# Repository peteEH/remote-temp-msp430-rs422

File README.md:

# remote-temp-msp430-rs422
Remote Temperature Sensor Node - TMP10 - RS-422 or RS-485 based - MSP430G2553

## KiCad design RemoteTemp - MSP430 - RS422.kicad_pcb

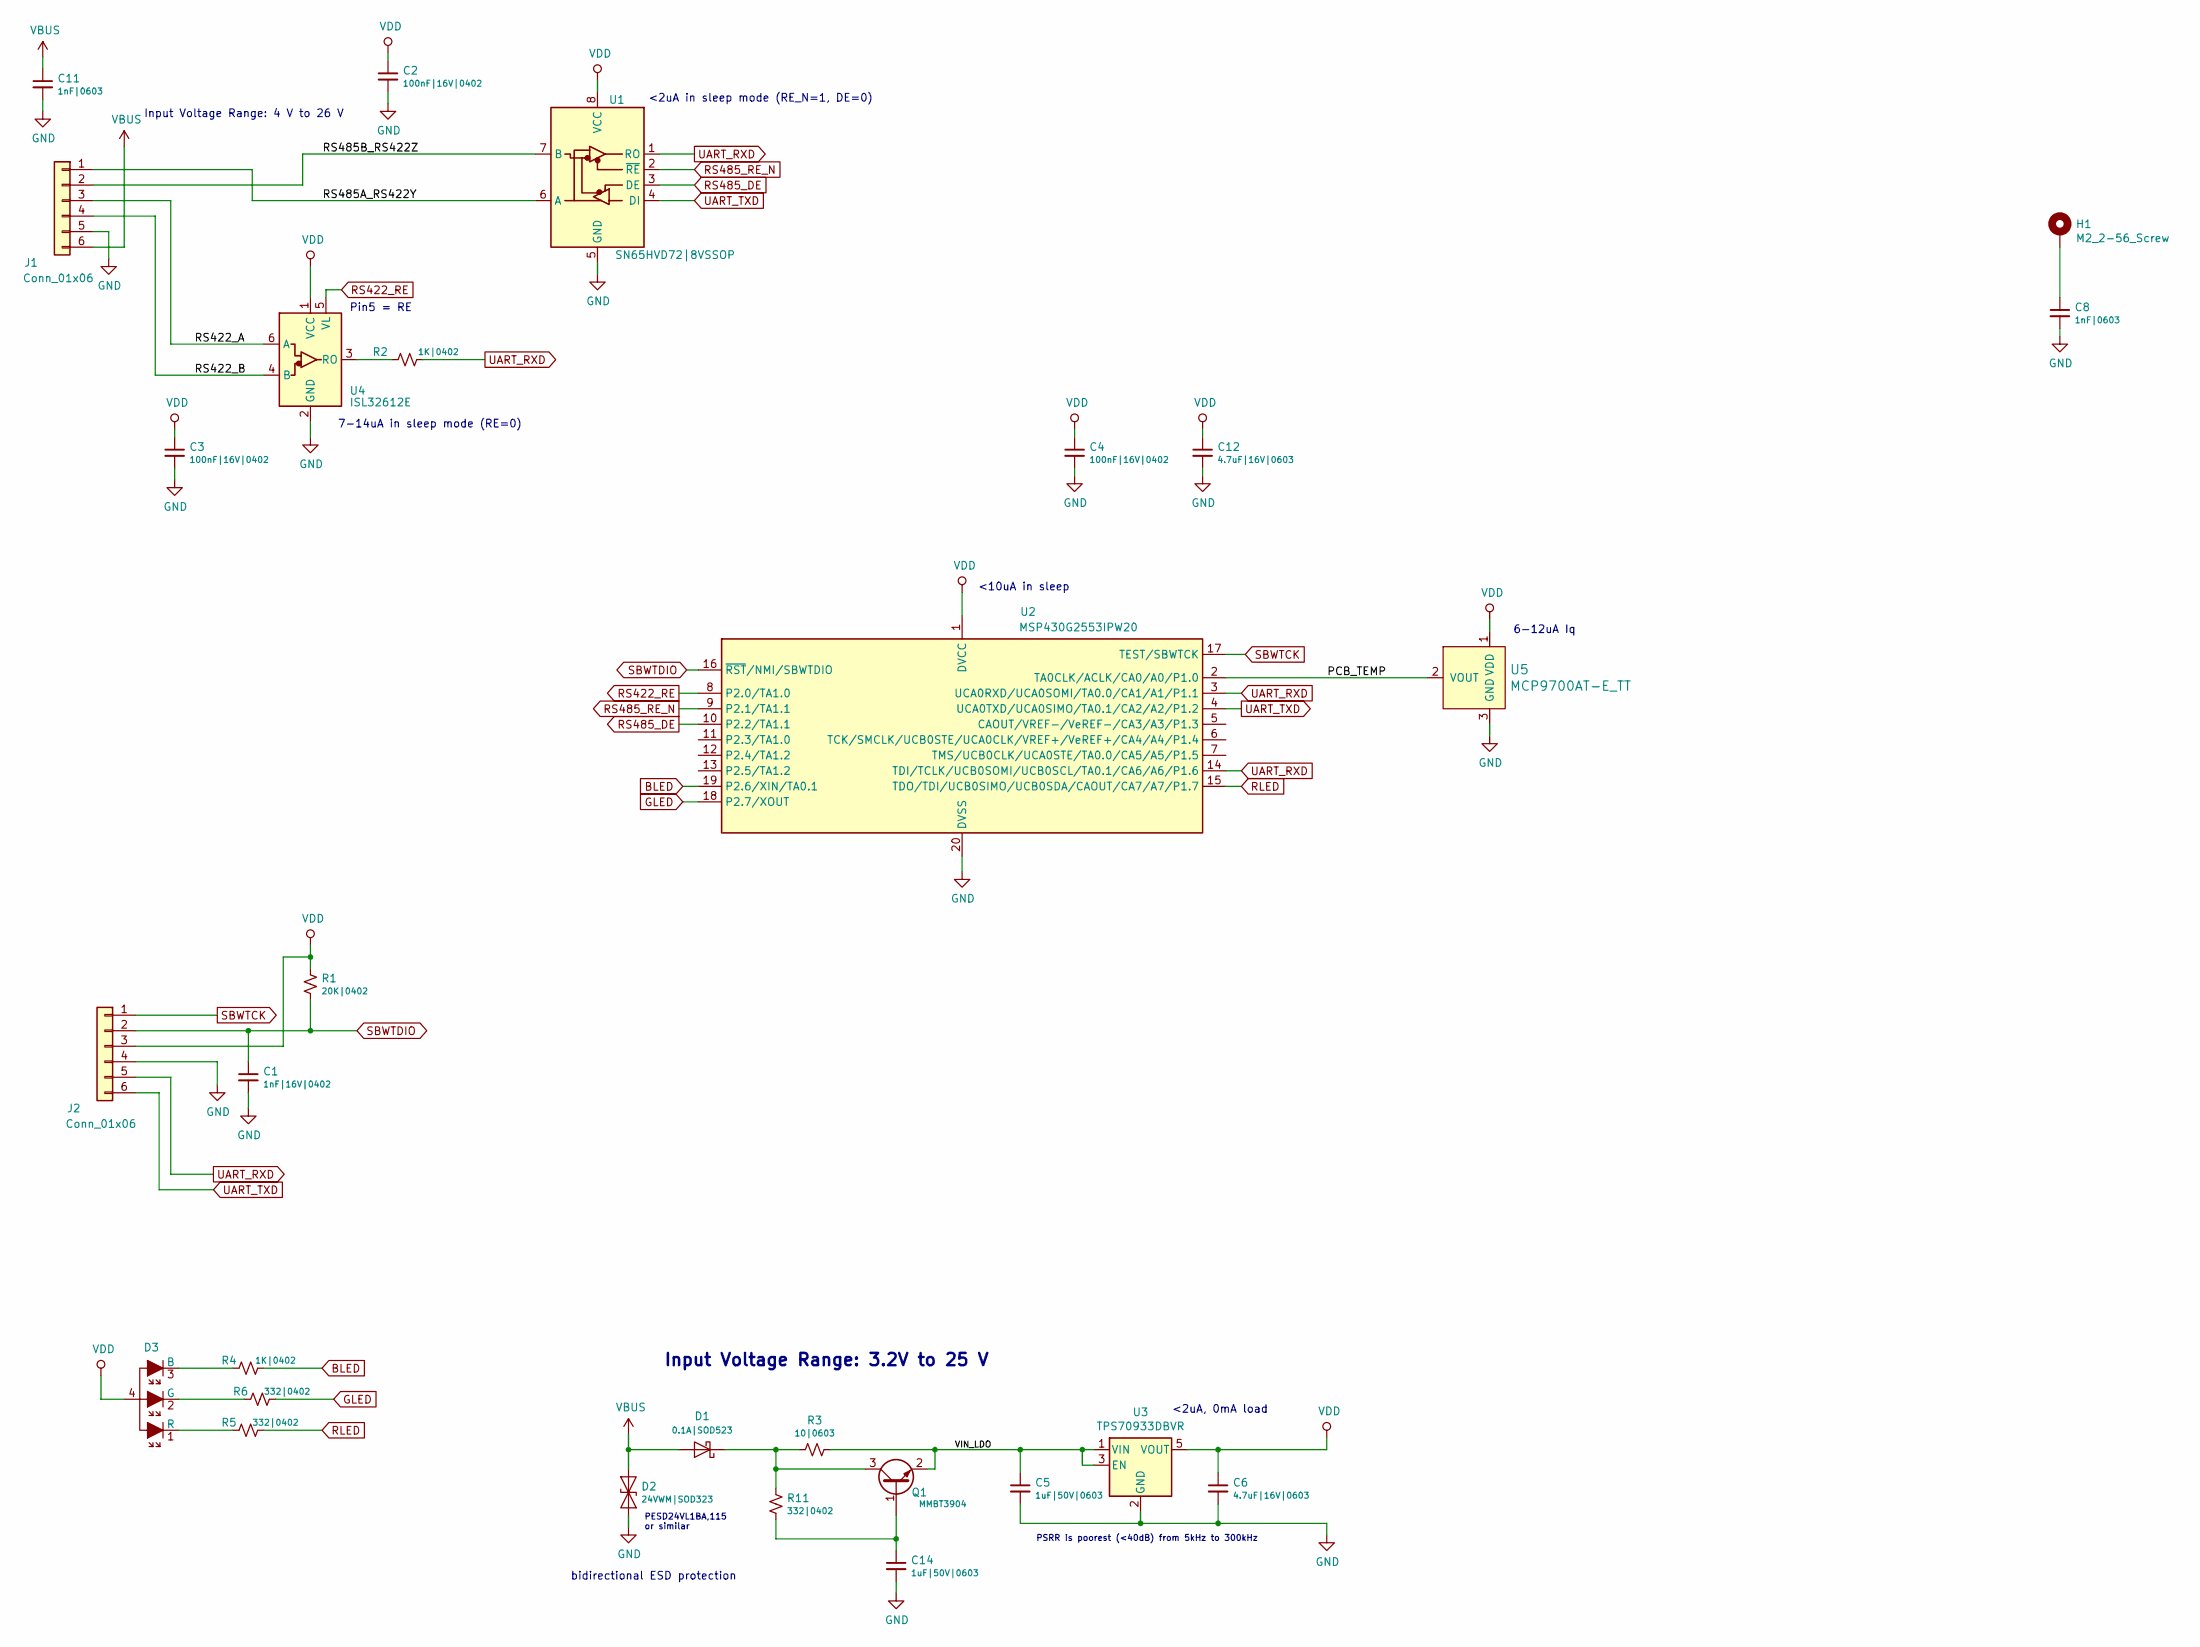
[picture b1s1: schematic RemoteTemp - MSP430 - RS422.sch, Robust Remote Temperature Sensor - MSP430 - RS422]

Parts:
C1: 1nF|16V|0402; C_0402_1005Metric
C2, C3, C4: 100nF|16V|0402; C_0402_1005Metric
C5, C14: 1uF|50V|0603; C_0603_1608Metric
C6, C12: 4.7uF|16V|0603; C_0603_1608Metric
C8, C11: 1nF|0603; C_0603_1608Metric
D1: 0.1A|SOD523; D_SOD-523
D2: 24VWM|SOD323; D_SOD-323_HandSoldering
D3: LTST-C19HE1WT; LED_Dual0603; MPN LTST-C19HE1WT; Digi-Key_PN 160-2162-1-ND
H1: M2_2-56_Screw; MountingHole_2.5mm_Pad
J1, J2: Conn_01x06; PinHeader_1x06_P2.54mm_Vertical
Q1: MMBT3904; SOT-23
R1: 20K|0402; R_0402_1005Metric
R2, R4: 1K|0402; R_0402_1005Metric
R3: 10|0603; R_0603_1608Metric_Pad1.05x0.95mm_HandSolder
R5, R6, R11: 332|0402; R_0402_1005Metric
U1: SN65HVD72|8VSSOP; MSOP-8_3x3mm_P0.65mm
U2: MSP430G2553IPW20; TSSOP-20_4.4x6.5mm_P0.65mm
U3: TPS70933DBVR; SOT-23-5
U4: ISL32612E; SOT-23-6
U5: MCP9700AT-E_TT; SOT-23-3; MPN MCP9700AT-E/TT; Digi-Key_PN MCP9700AT-E/TTCT-ND

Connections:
/PCB_TEMP: U2.2 (TA0CLK/ACLK/CA0/A0/P1.0), U5.2 (VOUT)
/RS422_A: J1.3, U4.6 (A)
/RS422_B: J1.4, U4.4 (B)
/RS485A_RS422Y: J1.1, U1.6 (A)
/RS485B_RS422Z: J1.2, U1.7 (B)
/VIN_LDO: C5.1, Q1.2 (E), R3.1, U3.1 (VIN), U3.3 (EN)
BLED: R4.1, U2.19 (P2.6/XIN/TA0.1)
GLED: R6.1, U2.18 (P2.7/XOUT)
GND: C1.2, C2.2, C3.2, C4.2, C5.2, C6.2, C8.2, C11.2, C12.2, C14.2, D2.2 (A2), J1.5, J2.4, U1.5 (GND), U2.20 (DVSS), U3.2 (GND), U4.2 (GND), U5.3 (GND)
unnamed: C8.1, H1.1
unnamed: C14.1, Q1.1 (B), R11.2
unnamed: D1.1 (K), Q1.3 (C), R3.2, R11.1
unnamed: D3.1 (R), R5.2
unnamed: D3.2 (G), R6.2
unnamed: D3.3 (B), R4.2
unnamed: R2.2, U4.3 (RO)
RLED: R5.1, U2.15 (TDO/TDI/UCB0SIMO/UCB0SDA/CAOUT/CA7/A7/P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)
RS422_RE: U2.8 (P2.0/TA1.0), U4.5 (VL)
RS485_DE: U1.3 (DE), U2.10 (P2.2/TA1.1)
RS485_RE_N: U1.2 (~RE), U2.9 (P2.1/TA1.1)
SBWTCK: J2.1, U2.17 (TEST/SBWTCK)
SBWTDIO: C1.1, J2.2, R1.2, U2.16 (~RST~/NMI/SBWTDIO)
UART_RXD: J2.5, R2.1, U1.1 (RO), U2.3 (UCA0RXD/UCA0SOMI/TA0.0/CA1/A1/P1.1), U2.14 (TDI/TCLK/UCB0SOMI/UCB0SCL/TA0.1/CA6/A6/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)
UART_TXD: J2.6, U1.4 (DI), U2.4 (UCA0TXD/UCA0SIMO/TA0.1/CA2/A2/P1.2)
VBUS: C11.1, D1.2 (A), D2.1 (A1), J1.6
VDD: C2.1, C3.1, C4.1, C6.1, C12.1, D3.4, J2.3, R1.1, U1.8 (VCC), U2.1 (DVCC), U3.5 (VOUT), U4.1 (VCC), U5.1 (VDD)

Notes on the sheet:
Input Voltage Range: 3.2V to 25 V
Input Voltage Range: 4 V to 26 V
PESD24VL1BA,115 or similar
PSRR is poorest (<40dB) from 5kHz to 300kHz
bidirectional ESD protection
7-14uA in sleep mode (RE=0)
Pin5 = RE
<2uA in sleep mode (RE_N=1, DE=0)
<10uA in sleep
6-12uA Iq
<2uA, 0mA load

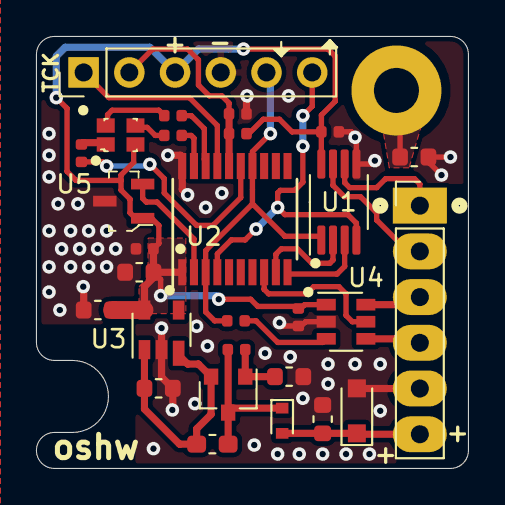
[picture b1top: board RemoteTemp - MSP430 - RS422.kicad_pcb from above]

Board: 2 copper layers, 24.0 x 24.0 mm, 29 parts (0 on the bottom side), 26 nets.

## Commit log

2021-08-06 initial file upload - V1.0
2021-08-06 remove pdf
